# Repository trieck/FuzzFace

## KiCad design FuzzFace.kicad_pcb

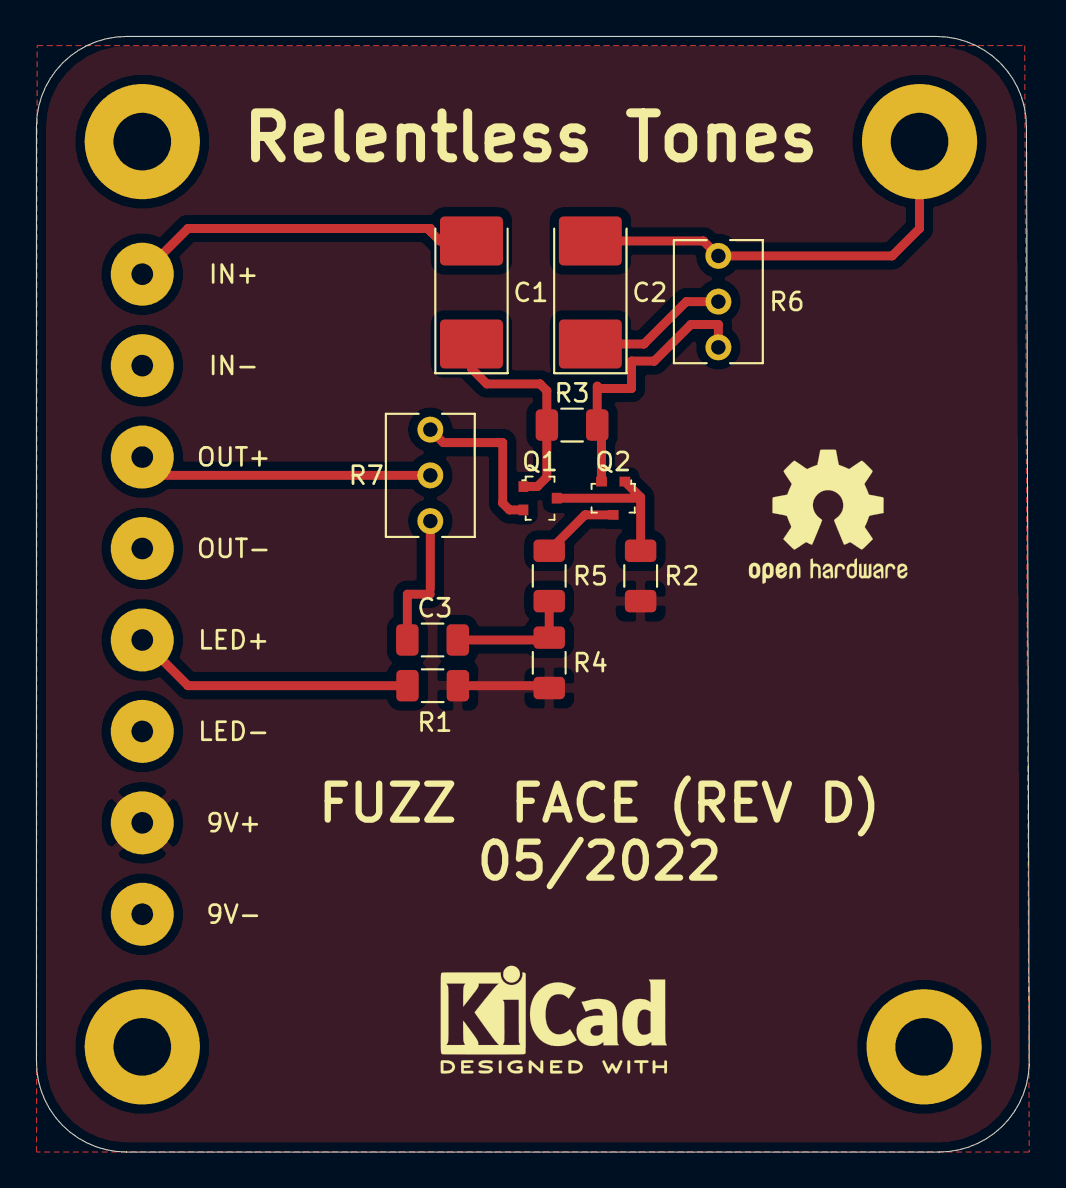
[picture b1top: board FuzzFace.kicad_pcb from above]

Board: 2 copper layers, 55.2 x 62.0 mm, 20 parts (0 on the bottom side), 12 nets.

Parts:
+9V1: +9V; SolderWirePad_1x01_Drill1.2mm
C1: 2.2uF; CP_EIA-7132-28_AVX-C_Pad2.72x3.50mm_HandSolder
C2: 22uF; CP_EIA-7132-28_AVX-C_Pad2.72x3.50mm_HandSolder
C3: 0.01u; C_1206_3216Metric
EARTH: IN; SolderWirePad_1x01_Drill1.2mm
EARTH#2, EARTH#3, EARTH#4: IN; SolderWirePad_1x01_Drill1.2mm
IN1: IN; SolderWirePad_1x01_Drill1.2mm
LED1: LED; SolderWirePad_1x01_Drill1.2mm
OUT1: OUT; SolderWirePad_1x01_Drill1.2mm
Q1, Q2: MMBT3904WT1G; SOT-323
R1: 470; R_1206_3216Metric
R2: 33K; R_1206_3216Metric
R3: 100K; R_1206_3216Metric
R4: 330; R_1206_3216Metric
R5: 8K2; R_1206_3216Metric
R6: 1K; Potentiometer_Vishay_T73XW_Horizontal
R7: 500K; Potentiometer_Vishay_T73XW_Horizontal

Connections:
Earth: C2.2, EARTH.1, EARTH#2.1, EARTH#3.1, EARTH#4.1, Q1.2, R6.3, R7.3
unnamed: +9V1.1, R1.2, R2.2, R4.1
unnamed: C1.1, Q1.1, R3.1
unnamed: C1.2, IN1.1
unnamed: C2.1, R6.2
unnamed: C3.1, R7.1
unnamed: C3.2, R4.2, R5.2
unnamed: LED1.1, R1.1
unnamed: OUT1.1, R7.2
unnamed: Q1.3, Q2.1, R2.1
unnamed: Q2.2, R3.2, R6.1
unnamed: Q2.3, R5.1

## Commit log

2022-06-01 Initial commit.
